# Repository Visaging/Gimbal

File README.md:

# Over-Engineered Stick (ESP32-S3 Gimbal)
Because apparently holding a phone parallel to the ground requires too much caloric burn for the modern human, I spent some time engineering a robot to do it for me. This is a custom 3-axis gimbal powered by an ESP32-S3, designed to compensate for your lack of wrist stability and general unwillingness to hold a steady shot.

## The "Why Did I Build This" Stack:
- **MCU:** ESP32-S3-WROOM-1-N8R2 _(Because a simple Arduino wasn't overkill enough)_
- **Sensors:** BMI270 6-Axis IMU _(To feel every single one of your hand tremors)_
- **Drivers:** 3x DRV8313 Three-Phase Drivers _(So the phone floats magically while you do nothing)_
- **Motors:** 2805 140KV Gimbal BLDC Motors _(To turn in exactly the opposite direction like she did)_
- **Power:** Custom 3S Li-Ion BMS with CN3303 Charging & TPS563200 Regulation _(Because USB 5V is for the weak)_

## Key Features
- **Active Stabilization:** Uses high-frequency FOC math to micro-manage gravity so you don't have to use "muscles".
- **Native USB-C:** One cable to code it and charge it, because looking for two different cables is just too much work.
- **3 Operation Modes:**
   * Stabilize: Standard horizon leveling and pan following.
   * Teaching Mode: Disables the motors so you can twist the camera to any weird angle by hand. After 5 seconds of holding it there, the gimbal accepts its new reality and locks that position.
   * Selfie/Statue Mode: A dedicated mode that gives you 6 seconds to pose the camera, then freezes it in place indefinitely because apparently holding a selfie angle is considered cardio now.
<hr></hr>
<details>
  <summary><h2>External Wiring Diagrams</h2></summary>
  
### Battery:

<!--
https://mermaid.live/edit#pako:eNp1UU1PgzAY_ivNe2IZXUpZB_RgIsOPGL3ozXBp1g7IoF0qOHXbf7eAW5aot_f5Prx7WBmpgAPGONcIrYxeVwXvT4RqYzYclULLzIqdzvVgWtdmtyqFbdHj8-i79paqrlEwwfjqMH1Xh3Qk6JlYjkQ4-Sdw66U9wNkfOnb6jZfiQffSp5efkl8jd15KL0rOmyf93kunF3rm-IeAgA-FrSTwtajflA-Nso3oMex7Xw5tqRqVA3enFHaTQ66PLrQV-tWYBnhrOxezpivKE-i2UrQqq0RhRXNutkpLZZem0y1wFgwVwPfwATyIwtmCkGQxp4tgHjLCfPh0NItnYZwklM3jiAYhYUcfvoZVMmNxGNGIEOoCMUsSH5SsWmOfxocOfz1-AyY-iIE
-->
<hr></hr>

### Handle wiring:

<!--
https://mermaid.live/edit#pako:eNqVkj1vgzAQhv_K6WaI-HIAD1WbkqVqlrZT5cXBDqCAHTlGaYr474Wkzhgpm8_3Ps_dcAOWWkik6Ps-UwClVrumovMToNV6T6HmShSGnxRT_6Fdq09lzY2Fr-KaBHh5HuBY84OkILatXzam9KDlW9lSYPihy7008HlqbFkzhNH3n97CxMGru_BGd1JZbs5zfNVbqxWETpI6R_GwI3KO2x7rhx2xc0TO8b6-v8nUd0yMHlamEUh3vD1KDztpOj7XOMw6hraWnWQ4c4KbPUOmxgk6cPWtdYfUmn7CjO6r2hX9QXAri4ZXhnc3s5FKSPOqe2WREnJRIB3wB2mYxotlEOTLJFqGSUyCqXuevkm2iLM8j0iSpVEYB2T08PcyNViQLE6jNAiiCchInnsoRWO12VyP6XJT4x85e7cJ
-->
<hr></hr>

### BMI270 Breakout Board:

<!--
https://mermaid.live/edit#pako:eNqNkctuwjAQRX_FmhVICTIxzsOLSoBR1fRBBbSLKhsLmySC2MhNRFvCv9cJatfs5lrnXGs0Z9gaqYCB7_uZRmhr9K7MWTcidDBmz1AhtORWnHSme2h3MKdtIWyNNvzKITQfzJ4fggij2WoxfVy-bdBsOV3xoe_ftfcvvE1jp_LBYv1KguEtEnknbZp00i30mk_bNLyZnj-1Ke1o8CC3pQS2E4dP5UGlbCW6DOeuKIO6UJXKgLlRCrvPINMXJx2F_jCmAlbbxmnWNHnxF5qjFLXipcitqP6brdJS2blpdA1sjKO-A9gZvlyMyCjEOAknQTieEIqpB9_umcYjEidJQCdxFIwJphcPfvpv8YjGJHLr4cAJMU0SD5Qsa2Ofr9fsj3r5BQMWhVA
-->
<hr></hr>

### Motors:

<!--
https://mermaid.live/edit#pako:eNp9kstqwzAQRX9FzKoGO1iSH7EW3dTtohC6STfFGxHJDxJLQZVJW8f_XsVJkxKDF4I7c-7cQTA9bLSQwCAIgkIhtNGqbCp2kgjttN4yVHMlcsMPqlCjqdzpw6bmxqJ1fvYh9IpxEDwe397X-Jg_rLTVBmFvSskspXf05iDX9OeLg3hTSmYpvaM3B72mv1wc1JtSMkvpPwo-VKYRwEq--5Q-tNK0_FRDPy4GW8tWFsCcFNxsCyjU4Ib2XH1o3QKzpnNjRndV_Vd0e8GtzBteGd5ek41UQpon3SkLDNN4zADWw5crE7LIsoyE0TKOQ0LSpQ_frh0lC_dwlCURzghOBx9-xq3hIqYhjtIwjROn0oT4IEXj_rQ638h4KsMv4dSfuQ
-->

</details>
<hr></hr>
<details>
  <summary><h2>PCB Schematics</h2></summary>

</details>
<hr></hr>
<details>
  <summary><h2>PCB Layout and Render</h2></summary>

</details>
<hr></hr>
<details>
  <summary><h2>Custom Body (3D Model)</h2></summary>

### Handle:

<hr></hr>

### Handle Top:

<hr></hr>

### Handle Enclosure:

<hr></hr>

### PAN Arm :

<hr></hr>

### ROLL Arm:

<hr></hr>

### PITCH Arm:

<hr></hr>

### PITCH Arm Cover:

<hr></hr>

### Tripod Enclosure:

<hr></hr>

### Tripod Hub:

<hr></hr>

### Tripod Legs:

</details>
<hr></hr>

## Financial Damage Report (Bill of Material)
BOM can be found in the  root older as a .csv, and is also viewable here: [Custom Gimble BOM](https://docs.google.com/spreadsheets/d/1aBBvSRlrgi5838ZnFZRnFuO4f2IFtYvHOy1n1r-4Mq0/edit?usp=sharing)
<details>
  <summary>Lion Circuits Order</summary>

</details>
<details>
  <summary>JLCPCB Order</summary>

</details>
<details>
  <summary>Carts</summary>
  
### Robu

<hr></hr>

### OnlyScrews

<hr></hr>

### ElectroPi

<hr></hr>

### Evalta

<hr></hr>

### DNA Tech India

<hr></hr>

### Amazon

</details>

## Future Bugs... I Mean Features (Roadmap)
Things I might add if I ever get bored of it working perfectly

- [ ] Bluetooth App: Control the gimbal with a phone _(because looking at two screens is better than one)._
- [ ] Face Tracking: If I can figure out how to run AI on this chip without it catching fire.

## Liability Waiver (License)
**License:** MIT

Feel free to steal this code, modify it, or sell it. However, if your phone falls out and breaks because you set the PID values wrong, I legally never met you.

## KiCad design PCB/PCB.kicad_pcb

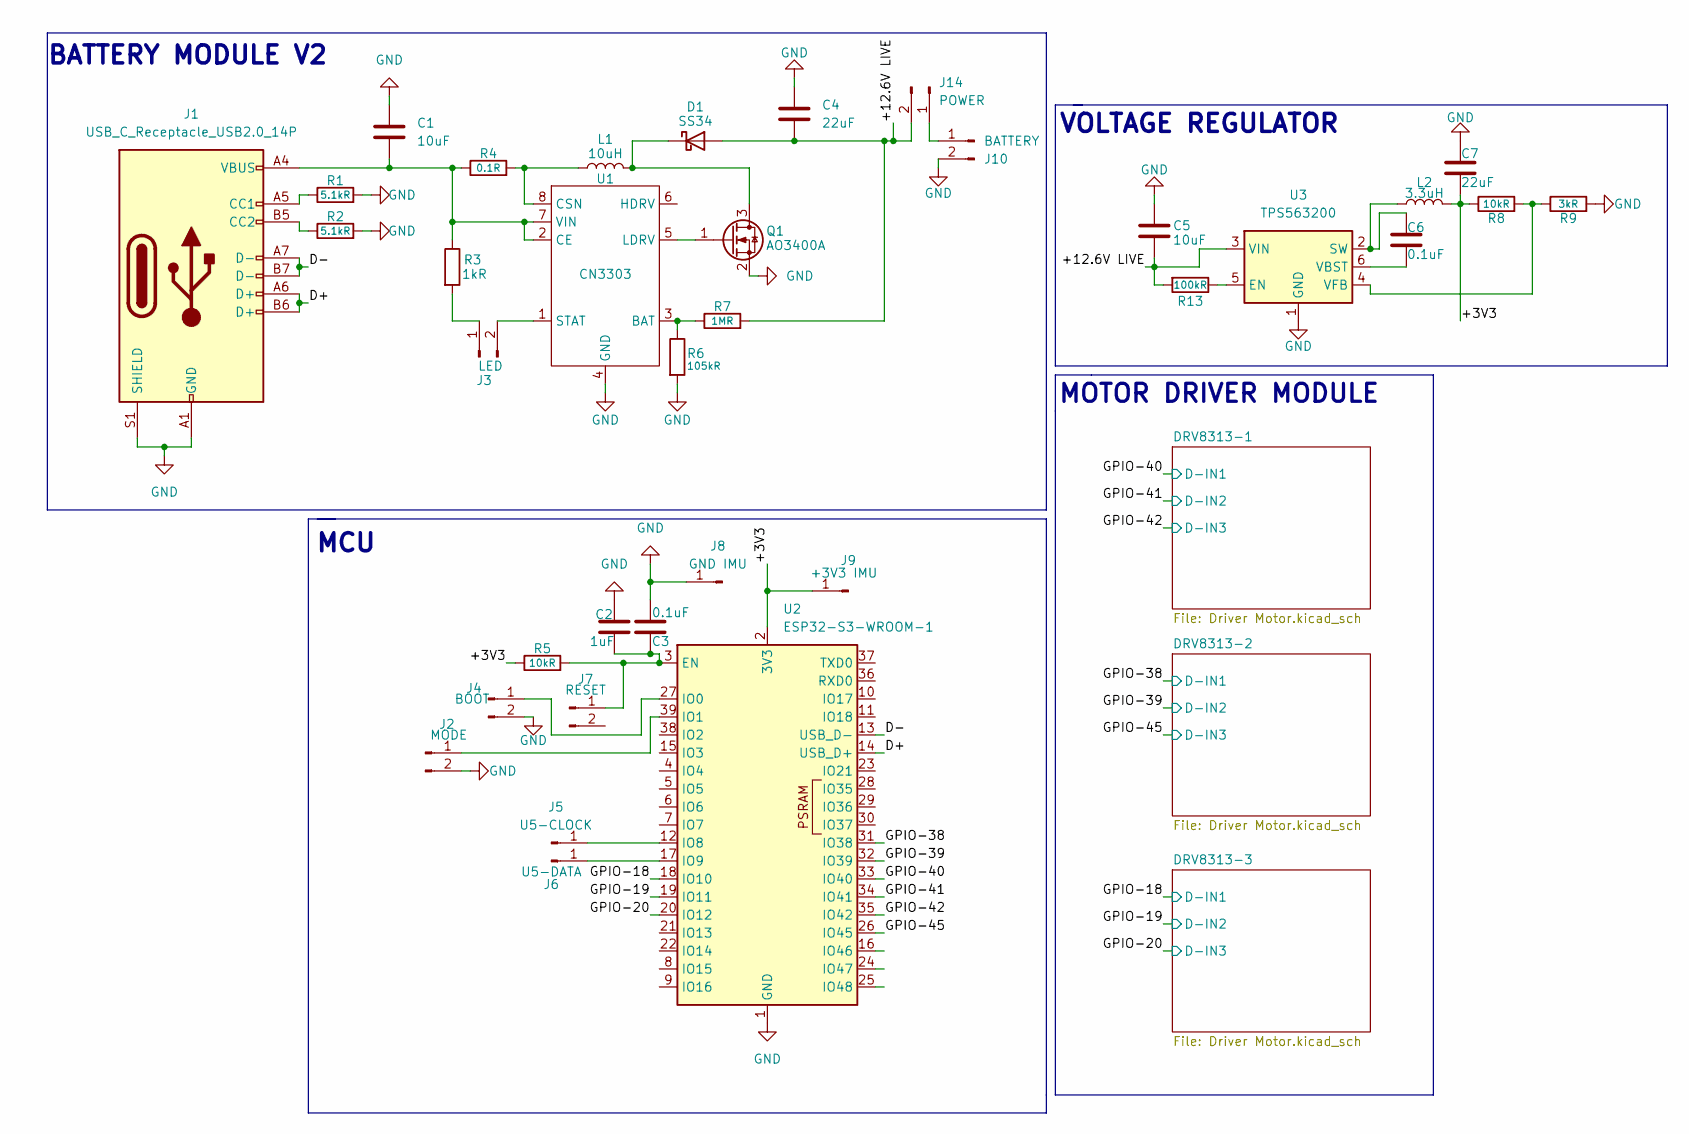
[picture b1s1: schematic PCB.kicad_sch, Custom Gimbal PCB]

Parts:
C1, C5: 10uF; C_0805_2012Metric
C2: 1uF; C_0805_2012Metric
C3, C6: 0.1uF; C_0805_2012Metric
C4, C7: 22uF; C_0805_2012Metric
D1: SS34; D_SMA
J1: USB_C_Receptacle_USB2.0_14P; USB_C_Receptacle_HRO_TYPE-C-31-M-12
J2: MODE; SolderWire-0.1sqmm_1x02_P3.6mm_D0.4mm_OD1mm
J3: LED; SolderWire-0.1sqmm_1x02_P3.6mm_D0.4mm_OD1mm
J4: BOOT; SolderWire-0.1sqmm_1x02_P3.6mm_D0.4mm_OD1mm
J5: U5-CLOCK; SolderWire-0.1sqmm_1x01_D0.4mm_OD1mm
J6: U5-DATA; SolderWire-0.1sqmm_1x01_D0.4mm_OD1mm
J7: RESET; SolderWire-0.1sqmm_1x02_P3.6mm_D0.4mm_OD1mm
J8: GND IMU; SolderWire-0.1sqmm_1x01_D0.4mm_OD1mm
J9: +3V3 IMU; SolderWire-0.1sqmm_1x01_D0.4mm_OD1mm
J10: BATTERY; SolderWire-0.1sqmm_1x02_P3.6mm_D0.4mm_OD1mm
J14: POWER; SolderWire-0.1sqmm_1x02_P3.6mm_D0.4mm_OD1mm
L1: 10uH; L_Bourns-SRN6028
L2: 3.3uH; L_1210_3225Metric
Q1: AO3400A; SOT-23
R1, R2: 5.1kR; R_0805_2012Metric_Pad1.20x1.40mm_HandSolder
R3: 1kR; R_0805_2012Metric
R4: 0.1R; R_1206_3216Metric
R5, R8: 10kR; R_0805_2012Metric
R6: 105kR; R_0805_2012Metric
R7: 1MR; R_0805_2012Metric
R9: 3kR; R_0805_2012Metric
R13: 100kR; R_0805_2012Metric
U1: CN3303; SOIC-8_3.9x4.9mm_P1.27mm
U2: ESP32-S3-WROOM-1
U3: TPS563200; SOT-23-6

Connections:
/+3V3: C7.1, J9.1, L2.2, R5.1, R8.1, U2.2 (3V3)
/+12.6V LIVE: C4.1, C5.2, D1.2 (A), J14.2, R7.2, R13.2, U3.3 (VIN)
/D+: J1.A6 (D+), J1.B6 (D+), U2.14 (USB_D+)
/D-: J1.A7 (D-), J1.B7 (D-), U2.13 (USB_D-)
/GPIO-18: U2.18 (IO10); also elsewhere on the board
/GPIO-19: U2.19 (IO11); also elsewhere on the board
/GPIO-20: U2.20 (IO12); also elsewhere on the board
/GPIO-38: U2.31 (IO38); also elsewhere on the board
/GPIO-39: U2.32 (IO39); also elsewhere on the board
/GPIO-40: U2.33 (IO40); also elsewhere on the board
/GPIO-41: U2.34 (IO41); also elsewhere on the board
/GPIO-42: U2.35 (IO42); also elsewhere on the board
/GPIO-45: U2.26 (IO45); also elsewhere on the board
GND: C1.1, C2.2, C3.2, C4.2, C5.1, C7.2, J1.A1 (GND), J1.A12 (GND), J1.B1 (GND), J1.B12 (GND), J1.S1 (SHIELD), J2.2, J4.2, J8.1, J10.2, Q1.2 (S), R1.2, R2.2, R6.2, R9.2, U1.4 (GND), U2.1 (GND), U2.40 (GND), U2.41 (GND), U3.1 (GND); also elsewhere on the board
unnamed: D1.1 (K), L1.2, Q1.3 (D)
unnamed: J1.A5 (CC1), R1.1
unnamed: J1.B5 (CC2), R2.1
unnamed: J2.1, U2.39 (IO1)
unnamed: J3.1, R3.2
unnamed: J3.2, U1.1 (STAT)
unnamed: J4.1, U2.27 (IO0)
unnamed: J5.1, U2.12 (IO8)
unnamed: J6.1, U2.17 (IO9)
unnamed: C2.1, C3.1, J7.1, R5.2, U2.3 (EN)
unnamed: J10.1, J14.1
unnamed: Q1.1 (G), U1.5 (LDRV)
unnamed: R6.1, R7.1, U1.3 (BAT)
unnamed: C1.2, J1.A4 (VBUS), J1.A9 (VBUS), J1.B4 (VBUS), J1.B9 (VBUS), R3.1, R4.1, U1.2 (CE), U1.7 (VIN)
unnamed: L1.1, R4.2, U1.8 (CSN)
unnamed: R13.1, U3.5 (EN)
unnamed: C6.1, L2.1, U3.2 (SW)
unnamed: C6.2, U3.6 (VBST)
unnamed: R8.2, R9.1, U3.4 (VFB)

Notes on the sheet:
MOTOR DRIVER MODULE
BATTERY MODULE V2
MCU
VOLTAGE REGULATOR

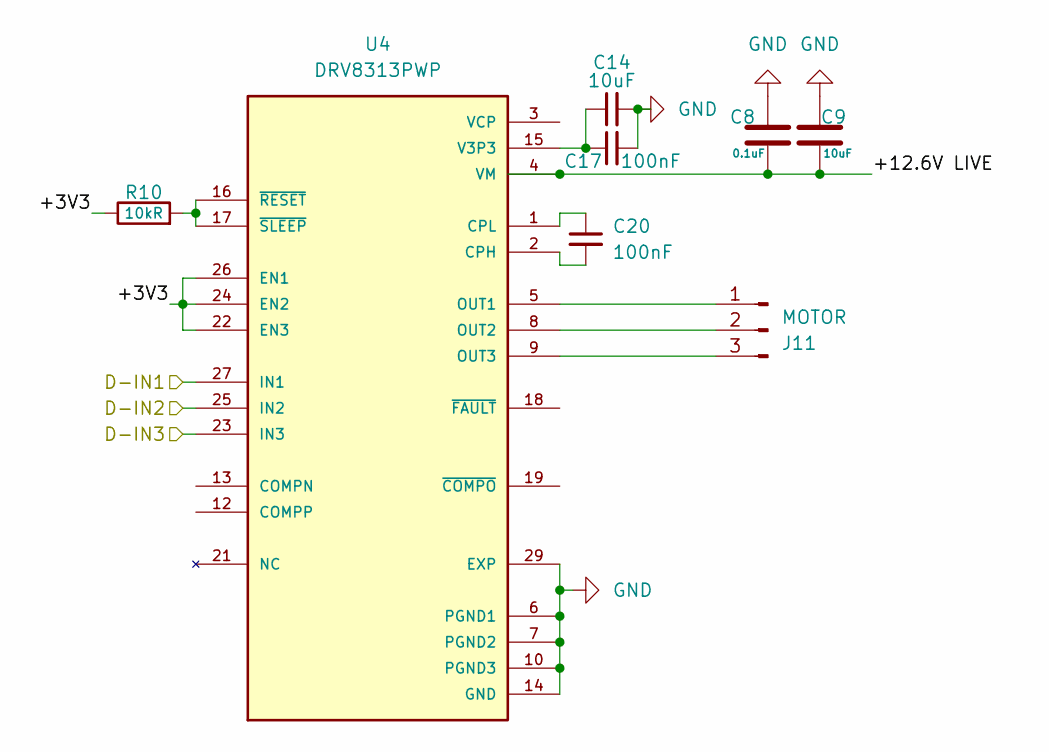
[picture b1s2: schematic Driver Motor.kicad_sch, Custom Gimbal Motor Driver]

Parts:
C8: 0.1uF; C_0805_2012Metric
C9, C14: 10uF; C_0805_2012Metric
C17, C20: 100nF; C_0805_2012Metric
J11: MOTOR; SolderWire-0.1sqmm_1x03_P3.6mm_D0.4mm_OD1mm
R10: 10kR; R_0805_2012Metric
U4: DRV8313PWP; SOP65P640X120-29N; PARTREV D

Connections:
/DRV8313-1/+3V3: R10.1, U4.22 (EN3), U4.24 (EN2), U4.26 (EN1)
/GPIO-40: U4.27 (IN1); also elsewhere on the board
/GPIO-41: U4.25 (IN2); also elsewhere on the board
/GPIO-42: U4.23 (IN3); also elsewhere on the board
GND: C8.2, C9.1, C14.2, C17.2, U4.6 (PGND1), U4.7 (PGND2), U4.10 (PGND3), U4.14 (GND), U4.20 (GND), U4.28 (GND), U4.29 (EXP); also elsewhere on the board
unnamed: J11.1, U4.5 (OUT1)
unnamed: J11.2, U4.8 (OUT2)
unnamed: J11.3, U4.9 (OUT3)
unnamed: C20.2, U4.2 (CPH)
unnamed: C20.1, U4.1 (CPL)
unnamed: C14.1, C17.1, U4.15 (V3P3)
unnamed: R10.2, U4.16 (~RESET), U4.17 (~SLEEP)
VM: C8.1, C9.2, U4.4 (VM), U4.11 (VM); also elsewhere on the board

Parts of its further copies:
C10, C12: 0.1uF; C_0805_2012Metric
C11, C13, C15, C16: 10uF; C_0805_2012Metric
C18, C19, C21, C22: 100nF; C_0805_2012Metric
J12, J13: MOTOR; SolderWire-0.1sqmm_1x03_P3.6mm_D0.4mm_OD1mm
R11, R12: 10kR; R_0805_2012Metric
U5, U6: DRV8313PWP; SOP65P640X120-29N; PARTREV D

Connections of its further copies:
/DRV8313-2/+3V3: R11.1, U5.22 (EN3), U5.24 (EN2), U5.26 (EN1)
/DRV8313-3/+3V3: R12.1, U6.22 (EN3), U6.24 (EN2), U6.26 (EN1)
/GPIO-18: U6.27 (IN1); also elsewhere on the board
/GPIO-19: U6.25 (IN2); also elsewhere on the board
/GPIO-20: U6.23 (IN3); also elsewhere on the board
/GPIO-38: U5.27 (IN1); also elsewhere on the board
/GPIO-39: U5.25 (IN2); also elsewhere on the board
/GPIO-45: U5.23 (IN3); also elsewhere on the board
GND: C10.2, C11.1, C12.2, C13.1, C15.2, C16.2, C18.2, C19.2, U5.6 (PGND1), U5.7 (PGND2), U5.10 (PGND3), U5.14 (GND), U5.20 (GND), U5.28 (GND), U5.29 (EXP), U6.6 (PGND1), U6.7 (PGND2), U6.10 (PGND3), U6.14 (GND), U6.20 (GND), U6.28 (GND), U6.29 (EXP); also elsewhere on the board
unnamed: J12.1, U5.5 (OUT1)
unnamed: J12.2, U5.8 (OUT2)
unnamed: J12.3, U5.9 (OUT3)
unnamed: J13.1, U6.5 (OUT1)
unnamed: J13.2, U6.8 (OUT2)
unnamed: J13.3, U6.9 (OUT3)
unnamed: C21.2, U5.2 (CPH)
unnamed: C21.1, U5.1 (CPL)
unnamed: C15.1, C18.1, U5.15 (V3P3)
unnamed: R11.2, U5.16 (~RESET), U5.17 (~SLEEP)
unnamed: C22.2, U6.2 (CPH)
unnamed: C22.1, U6.1 (CPL)
unnamed: C16.1, C19.1, U6.15 (V3P3)
unnamed: R12.2, U6.16 (~RESET), U6.17 (~SLEEP)
VM: C10.1, C11.2, C12.1, C13.2, U5.4 (VM), U5.11 (VM), U6.4 (VM), U6.11 (VM); also elsewhere on the board

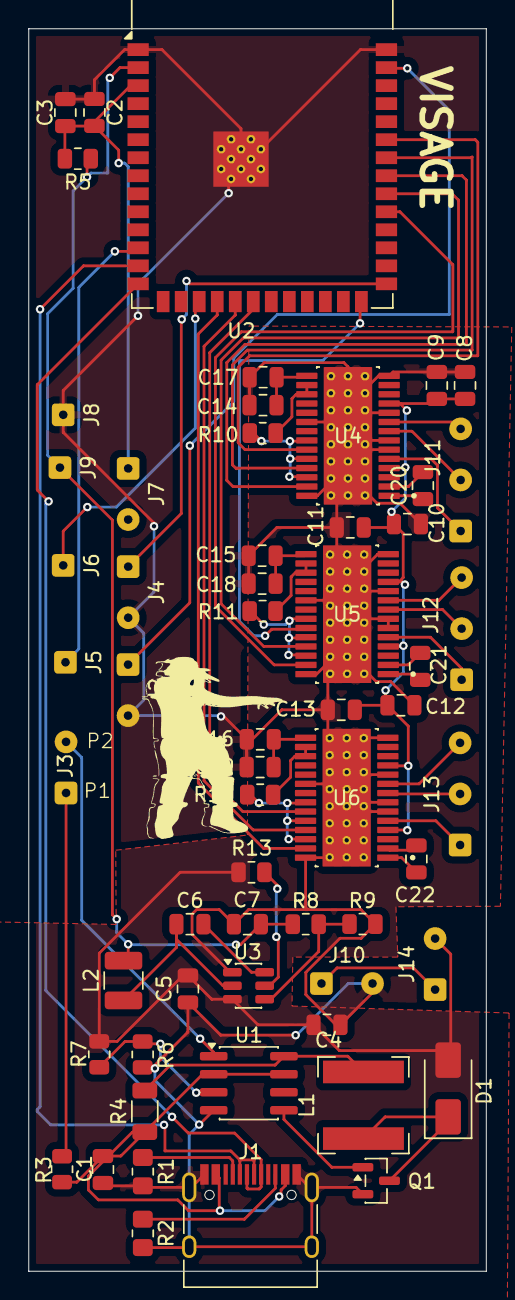
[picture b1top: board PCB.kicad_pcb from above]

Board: 2 copper layers, 32.2 x 87.6 mm, 59 parts (0 on the bottom side), 58 nets.

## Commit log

2026-01-19 Update README.md
    Added diagrams for battery, handle wiring, BMI270 breakout board, and motors.
